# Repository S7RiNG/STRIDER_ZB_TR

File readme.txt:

@STRIDER TEAM

本工程软件设计基于 MDK-ARM 和 STM32CubeMX
本工程PCB设计基于 kicad

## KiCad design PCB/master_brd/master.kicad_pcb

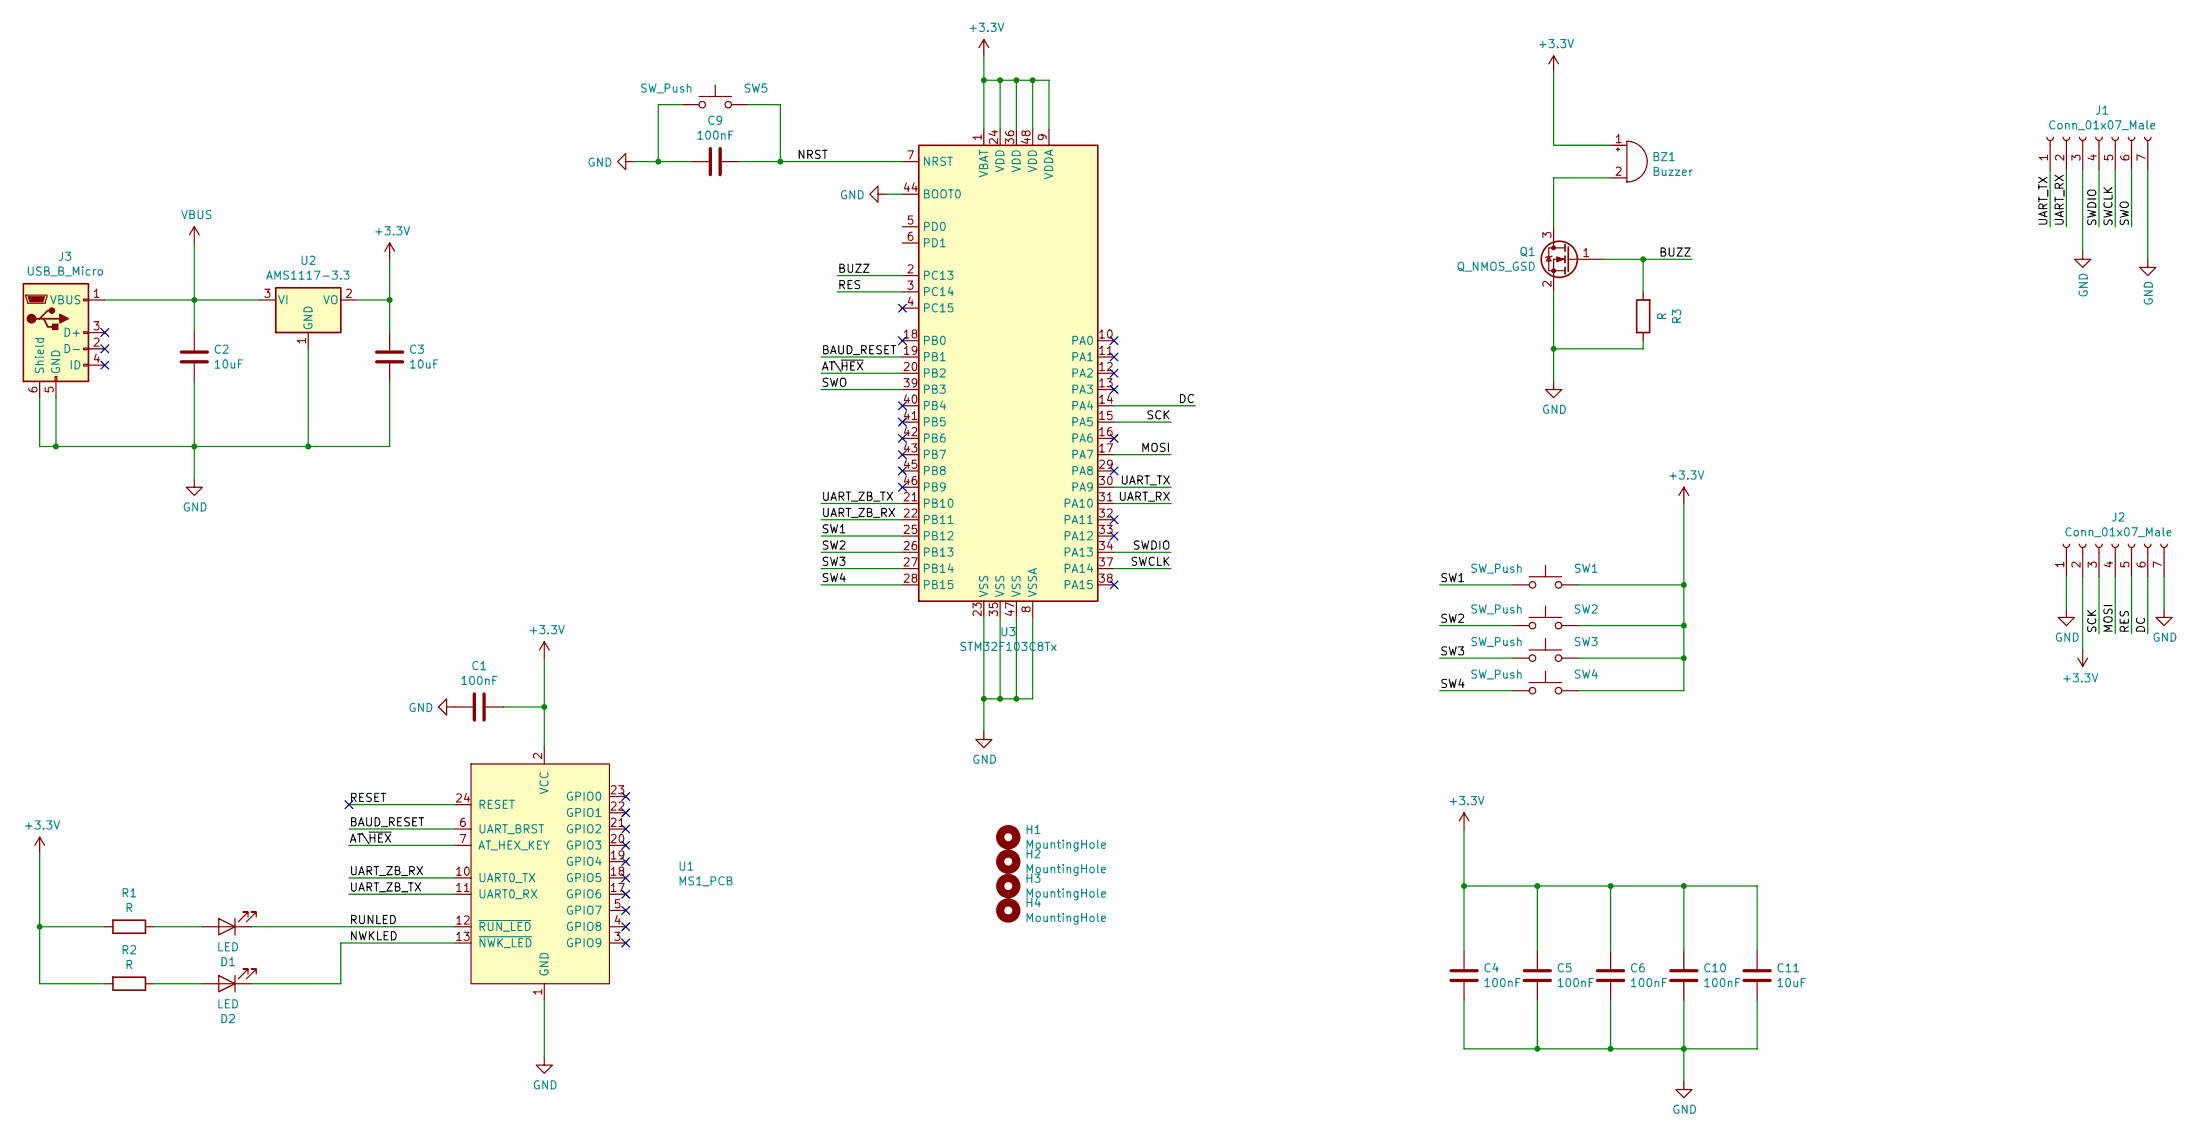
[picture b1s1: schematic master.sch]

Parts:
BZ1: Buzzer; CPA_2
C1, C4, C5, C6, C9, C10: 100nF; C_0805_2012Metric_Pad1.15x1.40mm_HandSolder
C2, C3, C11: 10uF; C_1206_3216Metric_Pad1.42x1.75mm_HandSolder
D1, D2: LED; LED_0805_2012Metric_Pad1.15x1.40mm_HandSolder
H1, H2, H3, H4: MountingHole; MountingHole_3.2mm_M3
J1, J2: Conn_01x07_Male; PinHeader_1x07_P2.54mm_Vertical
J3: USB_B_Micro; USB_microB
Q1: Q_NMOS_GSD; SOT-23
R1, R2, R3: R; R_0805_2012Metric_Pad1.15x1.40mm_HandSolder
SW1, SW2, SW3, SW4, SW5: SW_Push; SW_PUSH
U1: MS1_PCB
U2: AMS1117-3.3; SOT-223-3_TabPin2
U3: STM32F103C8Tx; LQFP-48_7x7mm_P0.5mm

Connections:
+3V3: BZ1.1 (-), C1.2, C3.1, C4.1, C5.1, C6.1, C10.1, C11.1, J2.2, R1.2, R2.2, SW1.2, SW2.2, SW3.2, SW4.2, U1.2 (VCC), U2.2 (VO), U3.1 (VBAT), U3.9 (VDDA), U3.24 (VDD), U3.36 (VDD), U3.48 (VDD)
/AT\~HEX~: U1.7 (AT_HEX_KEY), U3.20 (PB2)
/BAUD_RESET: U1.6 (UART_BRST), U3.19 (PB1)
/BUZZ: Q1.1 (G), R3.2, U3.2 (PC13)
/DC: J2.6, U3.14 (PA4)
/MOSI: J2.4, U3.17 (PA7)
/NRST: C9.1, SW5.2, U3.7 (NRST)
/NWKLED: D2.1 (K), U1.13 (~NWK_LED~)
/RES: J2.5, U3.3 (PC14)
/RESET: U1.24 (RESET)
/RUNLED: D1.1 (K), U1.12 (~RUN_LED~)
/SCK: J2.3, U3.15 (PA5)
/SW1: SW1.1, U3.25 (PB12)
/SW2: SW2.1, U3.26 (PB13)
/SW3: SW3.1, U3.27 (PB14)
/SW4: SW4.1, U3.28 (PB15)
/SWCLK: J1.5, U3.37 (PA14)
/SWDIO: J1.4, U3.34 (PA13)
/SWO: J1.6, U3.39 (PB3)
/UART_RX: J1.2, U3.31 (PA10)
/UART_TX: J1.1, U3.30 (PA9)
/UART_ZB_RX: U1.10 (UART0_TX), U3.22 (PB11)
/UART_ZB_TX: U1.11 (UART0_RX), U3.21 (PB10)
GND: C1.1, C2.2, C3.2, C4.2, C5.2, C6.2, C9.2, C10.2, C11.2, J1.3, J1.7, J2.1, J2.7, J3.5 (GND), J3.6 (Shield), Q1.2 (S), R3.1, SW5.1, U1.1 (GND), U2.1 (GND), U3.8 (VSSA), U3.23 (VSS), U3.35 (VSS), U3.44 (BOOT0), U3.47 (VSS)
unnamed: BZ1.2 (+), Q1.3 (D)
unnamed: D1.2 (A), R1.1
unnamed: D2.2 (A), R2.1
VBUS: C2.1, J3.1 (VBUS), U2.3 (VI)

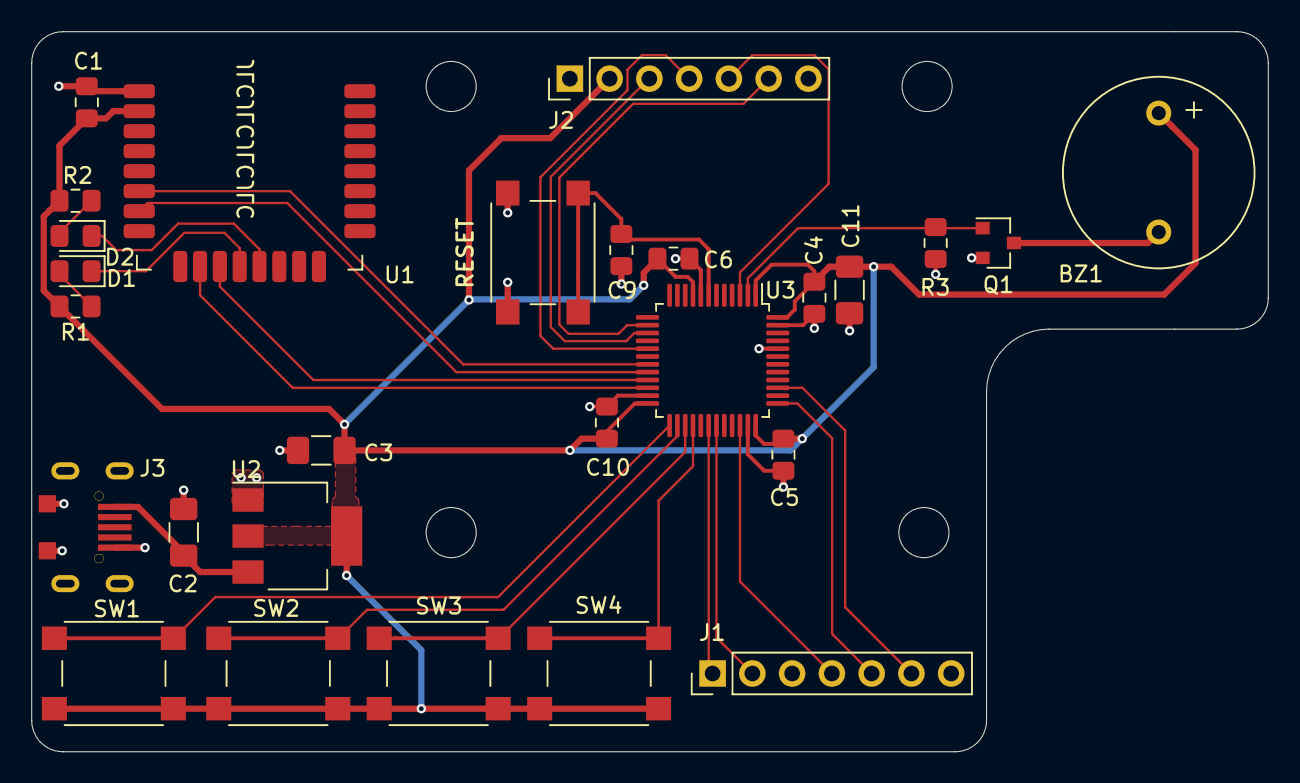
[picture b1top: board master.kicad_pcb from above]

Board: 2 copper layers, 79.0 x 46.0 mm, 31 parts (0 on the bottom side), 27 nets.

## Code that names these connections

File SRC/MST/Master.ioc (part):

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Mcu.Name=STM32F103C(8-B)Tx
Mcu.Package=LQFP48
Mcu.UserName=STM32F103C8Tx
PA10.GPIOParameters=GPIO_Label
PA10.GPIO_Label=UART_DEV_RX
PA10.Mode=Asynchronous
PA10.Signal=USART1_RX
PA13.Mode=Serial_Wire
PA13.Signal=SYS_JTMS-SWDIO
PA14.Mode=Serial_Wire
PA14.Signal=SYS_JTCK-SWCLK
PA4.GPIOParameters=GPIO_Speed,PinState,GPIO_Label
PA4.GPIO_Label=OLED_DC
PA4.GPIO_Speed=GPIO_SPEED_FREQ_HIGH
PA4.PinState=GPIO_PIN_SET
PA4.Signal=GPIO_Output
PA5.Mode=TX_Only_Simplex_Unidirect_Master
PA5.Signal=SPI1_SCK
PA7.Mode=TX_Only_Simplex_Unidirect_Master
PA7.Signal=SPI1_MOSI
PA9.GPIOParameters=GPIO_Label
PA9.GPIO_Label=UART_DEV_TX
PA9.Mode=Asynchronous
PA9.Signal=USART1_TX
PB10.GPIOParameters=GPIO_Label
PB10.GPIO_Label=UART_ZB_TX
PB10.Mode=Asynchronous
PB10.Signal=USART3_TX
PB11.GPIOParameters=GPIO_Label
PB11.GPIO_Label=UART_ZB_RX
PB11.Mode=Asynchronous
PB11.Signal=USART3_RX
PB12.GPIOParameters=GPIO_PuPd,GPIO_Label
PB12.GPIO_Label=SW1
PB12.GPIO_PuPd=GPIO_PULLDOWN
PB12.Signal=GPXTI12
PB13.GPIOParameters=GPIO_PuPd,GPIO_Label
PB13.GPIO_Label=SW2
PB13.GPIO_PuPd=GPIO_PULLDOWN
PB13.Signal=GPXTI13
PB14.GPIOParameters=GPIO_PuPd,GPIO_Label
PB14.GPIO_Label=SW3
PB14.GPIO_PuPd=GPIO_PULLDOWN
PB14.Signal=GPXTI14
PB15.GPIOParameters=GPIO_PuPd,GPIO_Label
PB15.GPIO_Label=SW4
PB15.GPIO_PuPd=GPIO_PULLDOWN
PB15.Signal=GPXTI15
PB2.GPIOParameters=GPIO_Speed,PinState,GPIO_PuPd,GPIO_Label,GPIO_ModeDefaultOutputPP
PB2.GPIO_Label=AT_HEX
PB2.GPIO_ModeDefaultOutputPP=GPIO_MODE_OUTPUT_PP
PB2.GPIO_PuPd=GPIO_NOPULL
PB2.GPIO_Speed=GPIO_SPEED_FREQ_LOW
PB2.PinState=GPIO_PIN_SET
PB2.Signal=GPIO_Output
PC13-TAMPER-RTC.GPIOParameters=GPIO_Label
PC13-TAMPER-RTC.GPIO_Label=BUZZ
PC13-TAMPER-RTC.Signal=GPIO_Output
PC14-OSC32_IN.GPIOParameters=GPIO_Speed,PinState,GPIO_Label
PC14-OSC32_IN.GPIO_Label=OLED_RES
PC14-OSC32_IN.GPIO_Speed=GPIO_SPEED_FREQ_HIGH
PC14-OSC32_IN.PinState=GPIO_PIN_SET
PC14-OSC32_IN.Signal=GPIO_Output
RCC.SYSCLKFreq_VALUE=64000000
RCC.SYSCLKSource=RCC_SYSCLKSOURCE_PLLCLK
board=custom

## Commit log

2019-12-29 change liwnse
